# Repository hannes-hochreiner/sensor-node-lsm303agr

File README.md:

# sensor-node-lsm303agr

A breakout board for the sensor node featuring the LSM303AGR

## Size Constraint

measured from the center of the sensor connector:
top: 16.5 mm
bottom: 4.5 mm
sides: 7.5 mm

## Main parts

### Sensor
  * STMicroelectronics: LSM303AGRTR
  * Digi-Key: [497-16527-1-ND](https://www.digikey.de/product-detail/de/stmicroelectronics/LSM303AGRTR/497-16527-1-ND/6006105)
  * [Datasheet](http://www.st.com/content/ccc/resource/technical/document/datasheet/74/c4/19/54/62/c5/46/13/DM00177685.pdf/files/DM00177685.pdf/jcr:content/translations/en.DM00177685.pdf)
  * [Application Note](https://www.st.com/resource/en/application_note/dm00265383.pdf)
  * Price: 2.39

## Passives

### Capacitor 220nF

CAP CER 0.22UF 16V X5R 0603

  * Taiyo Yuden: EMK107BJ224KAHT
  * Digi-Key: [587-3310-1-ND](https://www.digikey.de/product-detail/en/taiyo-yuden/EMK107BJ224KAHT/587-3310-1-ND/4157237)
  * [Datasheet](http://ds.yuden.co.jp/TYCOMPAS/ut/detail.do?productNo=EMK107BJ224KAHT&fileName=EMK107BJ224KAHT_SS&mode=specSheetDownload)
  * Price: 0.01

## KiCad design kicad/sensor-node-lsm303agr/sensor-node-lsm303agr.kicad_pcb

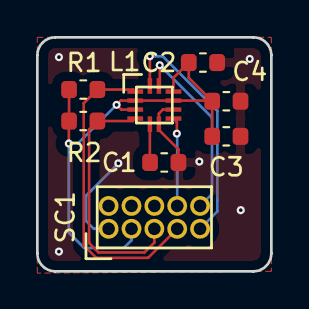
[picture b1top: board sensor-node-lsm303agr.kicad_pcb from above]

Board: 2 copper layers, 13.0 x 13.0 mm, 8 parts (0 on the bottom side), 8 nets.

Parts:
C1: 220nF; C_0603_1608Metric
C2, C4: 0.1µF; C_0603_1608Metric
C3: 10µF; C_0603_1608Metric
L1: LSM303AGR; lsm303agr
R1, R2: 10k; R_0603_1608Metric
SC1: Sensor-Connector; sensor-connector-male

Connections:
/3V3: C2.2, C3.2, C4.2, L1.2, L1.3, L1.9, L1.10, R1.1, R2.1, SC1.3
/DRDY: L1.7, SC1.8
/INT_1: L1.12, SC1.9
/INT_2: L1.11, SC1.10
/SCL: L1.1, R1.2, SC1.7
/SDA: L1.4, R2.2, SC1.5
GND: C1.2, C2.1, C3.1, C4.1, L1.6, L1.8, SC1.1
unnamed: C1.1, L1.5

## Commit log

2018-12-02 finished routing
2018-12-08 added application note
